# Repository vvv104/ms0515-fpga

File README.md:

# ms0515-fpga

The Elektronika MS 0515 rebuilt in an FPGA down to its circuits: the
system module НС4 (`3.858.420 Э3`) as a netlist of its chips, wired as the
schematic and the board wire them, tested against the emulator
(https://github.com/vvv104/ms0515).

- `docs/sources.md` - the documents, scans and threads it is read from
- `docs/plan.md` - the stages
- `docs/findings.md` - where the sources disagree
- `CLAUDE.md` - the rules of the repository

## The ready files

The releases (https://github.com/vvv104/ms0515-fpga/releases) carry the
MiSTer core (`ms0515.rbf`, for a DE10-Nano) and both printed boards'
Gerbers with their assembly drawings (НС4 and the RAM-disk module);
`docs/release.md` says what to do with each and how to make them again.

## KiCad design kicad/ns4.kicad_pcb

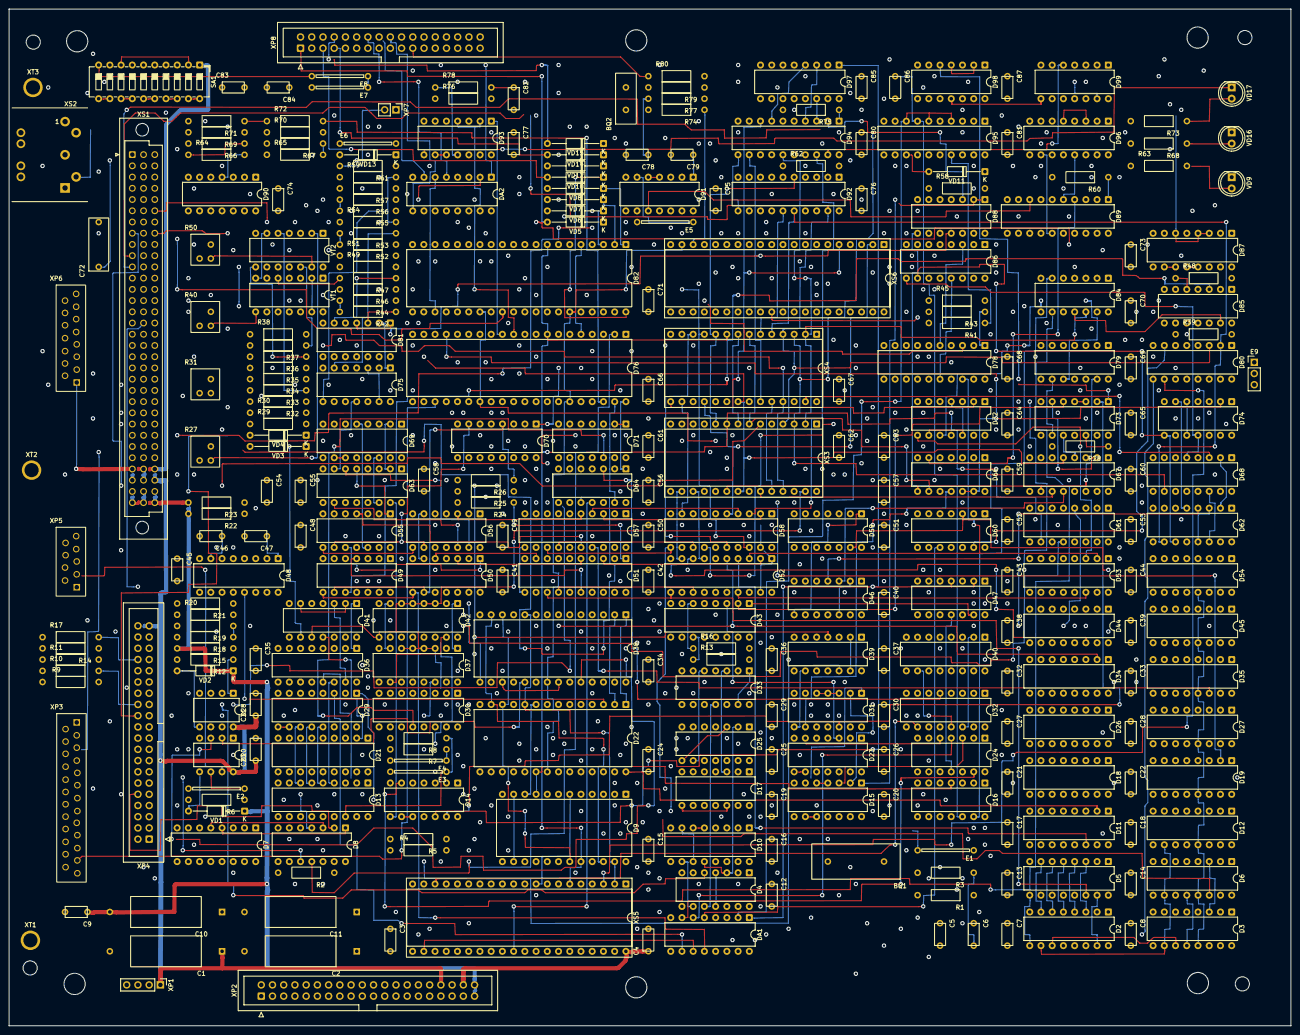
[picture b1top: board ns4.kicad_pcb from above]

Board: 8 copper layers, 290.0 x 230.0 mm, 324 parts (0 on the bottom side), 490 nets.

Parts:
BQ1: 8 МГц; Crystal_RK353_P12.70mm
BQ2: 15 МГц; Crystal_RK169_P5.08mm
C1, C2, C10, C11: 16В 33 мкФ ±20%; CP_Axial_P25.40mm
C3, C4, C7, C8, C9, C12, C13, C14, C15, C16, C17, C18, C19, C20, C21, C22, C23, C24, C25, C26, C27, C28, C29, C30, C31, C32, C33, C34, C36, C37, C38, C39, C41, C42, C43, C44, C48, C49, C50, C51, C52, C53, C55, C56, C57, C58, C59, C60, C61, C62, C63, C65, C66, C67, C68, C69, C71, C73, C75, C76, C77, C80, C81, C85, C87: 0,22 мкФ +80-20%; C_Disc_P5.08mm
C5, C6, C70: 100 пФ ±10%; C_Disc_P5.08mm
C35: 68 пФ ±10%; C_Disc_P5.08mm
C40: 27 пФ ±10%; C_Disc_P5.08mm
C45, C46, C47, C74: 2200 пФ ±10%; C_Disc_P5.08mm
C54: 4700 пФ ±10%; C_Disc_P5.08mm
C64: 120 пФ ±10%; C_Disc_P5.08mm
C72: 2,2 мкФ +80-20%; C_Rect_P10.16mm
C78, C79, C82: 51 пФ ±10%; C_Disc_P5.08mm
C83, C84, C86: 0,1 мкФ +80-20%; C_Disc_P5.08mm
D2, D3, D5, D6, D11, D12, D18, D19, D26, D27, D34, D35, D44, D45, D53, D54: КР565РУ5Г; DIP-16_W7.62mm
D4: К555ТЛ2; DIP-14_W7.62mm
D7: КР531ИД14; DIP-16_W7.62mm
D8: К155ЛП9; DIP-14_W7.62mm
D9: КР580ВИ53; DIP-24_W15.24mm
D10, D97: К555ТМ9; DIP-16_W7.62mm
D13, D21: КР556РТ12; DIP-18_W7.62mm
D14, D66: К555ЛА3; DIP-14_W7.62mm
D15, D91, D99: К555ЛН1; DIP-14_W7.62mm
D16, D46, D59: К555ИЕ19; DIP-14_W7.62mm
D17, D33, D41, D47, D60: К555ТМ2; DIP-14_W7.62mm
D20, D28: КР1102АП15; DIP-8_W7.62mm
D22, D38: КР580ВВ51А; DIP-28_W15.24mm
D23: КР531ЛЕ1; DIP-14_W7.62mm
D24: КР531ТМ2; DIP-14_W7.62mm
D25: К555ЛР11; DIP-14_W7.62mm
D29, D30, D36, D37, D42: К555ИЕ10; DIP-16_W7.62mm
D31: К555ЛА4; DIP-14_W7.62mm
D32, D86: К555КП15; DIP-16_W7.62mm
D39: К555ЛП5; DIP-14_W7.62mm
D40, D43: К555ТМ8; DIP-16_W7.62mm
D48: КР559ИП11; DIP-16_W7.62mm
D49, D50, D55, D56: К555ИР16; DIP-14_W7.62mm
D51, D57, D78, D89: К555ИР23; DIP-20_W7.62mm
D52, D58: К555АП5; DIP-20_W7.62mm
D61, D62, D63, D67, D68, D69, D87: К555КП2; DIP-16_W7.62mm
D64: К555ЛН2; DIP-14_W7.62mm
D70: К555КП11; DIP-16_W7.62mm
D71: К555ЛИ6; DIP-14_W7.62mm
D72, D74, D79, D84: К555ЛЛ1; DIP-14_W7.62mm
D73: К555ЛИ1; DIP-14_W7.62mm
D75: К155ЛН5; DIP-14_W7.62mm
D76, D82: КР580ВВ55А; DIP-40_W15.24mm
D80: К555ИД7; DIP-16_W7.62mm
D81, D93: К555ЛА13; DIP-14_W7.62mm
D85: К555ЛИ3; DIP-14_W7.62mm
D88: К555ЛА2; DIP-14_W7.62mm
D90: К554СА3А; DIP-14_W7.62mm
D92, D94: К555ИР22; DIP-20_W7.62mm
D95: К555АП3; DIP-20_W7.62mm
D96: К555ИВ3; DIP-16_W7.62mm
D98: КР1533ТМ2; DIP-14_W7.62mm
DA1: 3-15-1 кОм ±10%; DIP-16_W7.62mm
DA2: 3-15-10 кОм ±10%; DIP-16_W7.62mm
E1, E2, E3, E4, E5, E6, E7, E8: jumper (two contacts on Э3); Wire_Link_P12.70mm
E9: jumper (three contacts); PinHeader_1x03_P2.54mm_Vertical
H1, H2, H3, H4, H5, H6: Hole_4.8mm_NPTH
H7, H8, H9, H10: Hole_3.2mm_NPTH
R1, R3, R77, R79: 560 Ом; R_Axial_P12.70mm
R2, R6, R12: 10 кОм; R_Axial_P12.70mm
R4, R5, R7, R8, R21, R26, R28, R39, R41, R48, R55, R58, R71, R72, R74, R76, R80: 1 кОм; R_Axial_P12.70mm
R9, R10, R11, R14, R17: 150 Ом; R_Axial_P12.70mm
R13, R16: 33 Ом; R_Axial_P12.70mm
R15, R22, R23: 23,7 кОм ±1%; R_Axial_P12.70mm
R18, R20, R64, R70: 4,7 кОм; R_Axial_P12.70mm
R19: 1,2 кОм; R_Axial_P12.70mm
R24, R25, R43, R45, R60, R62, R75: 20 Ом; R_Axial_P12.70mm
R27, R31, R40, R50: 330 Ом (trimmer); Trimmer_SP5-16VA
R29: 180 Ом; R_Axial_P12.70mm
R30, R33, R35: 24 Ом; R_Axial_P12.70mm
R32, R34, R36, R37, R38: 75 Ом; R_Axial_P12.70mm
R42, R47, R52, R56: 510 Ом; R_Axial_P12.70mm
R44, R49, R53: 390 Ом; R_Axial_P12.70mm
R46, R51, R54, R59: 220 Ом; R_Axial_P12.70mm
R57: 270 Ом; R_Axial_P12.70mm
R61: 43 Ом; R_Axial_P12.70mm
R63, R68, R73: 470 Ом; R_Axial_P12.70mm
R65: 470 кОм; R_Axial_P12.70mm
R66: 24 кОм; R_Axial_P12.70mm
R67: 2,2 кОм; R_Axial_P12.70mm
R69: 12 кОм; R_Axial_P12.70mm
R78: 620 Ом; R_Axial_P12.70mm
R81: 620 кОм ±5%
SA1: switch, 10 pairs; SW_DIP_SPSTx10_Slide_6.7x26.96mm_W7.62mm_P2.54mm_LowProfile
VD1, VD2, VD3, VD4, VD5, VD6, VD7, VD8, VD10, VD12, VD13, VD14, VD15: diode; D_DO-35_SOD27_P12.70mm_Horizontal
VD9, VD16, VD17: LED; LED_D5.0mm
VD11: zener 3,3 В; D_DO-35_SOD27_P12.70mm_Horizontal
VT1, VT2: transistor assembly; DIP-14_W7.62mm
W1: 0.07 мм²
XP1: plug, 4; PinHeader_1x04_P2.54mm_Vertical
XP2, XP4: plug, 40; IDC-Header_2x20_P2.54mm_Vertical
XP3: plug, 25; DSUB-25_ONP-ZhG-79
XP5: plug, 9; DSUB-9_ONP-ZhG-79
XP6: plug, 15; DSUB-15_ONP-ZhG-79
XP7: plug, 2; PinHeader_1x02_P2.54mm_Vertical
XP8: plug, 34; IDC-Header_2x17_P2.54mm_Vertical
XS1: socket, 96 (rows A, B, C of 32); DIN41612_C_3x32_Female_Vertical_THT
XS2: socket, 5; DIN-5_Socket_Horizontal
XS3, XS4: DIP socket for D65, D77; DIP-28_W15.24mm_Socket
XS5, XS6: DIP socket for D1, D83; DIP-40_W15.24mm_Socket
XT1, XT2, XT3: ground lug (ОБЩИЙ); Lug_3.2mm

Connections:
+5V: C2.1, C3.1, C7.1, C8.1, C11.1, C12.1, C13.1, C14.1, C15.1, C16.1, C17.1, C18.1, C19.1, C20.1, C21.1, C22.1, C24.1, C25.1, C26.1, C27.1, C28.1, C29.1, C30.1, C32.1, C33.1, C34.1, C36.1, C37.1, C38.1, C39.1, C41.1, C42.1, C43.1, C44.1, C48.1, C49.1, C50.1, C51.1, C52.1, C53.1, C55.1, C56.1, C57.1, C58.1, C59.1, C60.1, C61.1, C62.1, C63.1, C65.1, C66.1, C67.1, C68.1, C69.1, C71.1, C73.1, C74.1, C75.1, C76.1, C77.1, C80.1, C81.1, C85.1, C87.1, D2.8, D3.8, D4.14, D5.8, D6.8, D7.16, D8.14, D9.24, D10.16, D11.8, D12.8, D13.18, D14.14, D15.14, D16.14, D17.14, D18.8, D19.8, D21.18, D22.26, D23.14, D24.14, D25.14, D26.8, D27.8, D29.16, D30.16, D31.14, D32.16, D33.14, D34.8, D35.8, D36.16, D37.16, D38.26, D39.14, D40.16, D41.14, D42.16, D43.16, D44.8, D45.8, D46.14, D47.14, D48.16, D49.14, D50.14, D51.20, D52.20, D53.8, D54.8, D55.14, D56.14, D57.20, D58.20, D59.14, D60.14, D61.16, D62.16, D63.16, D64.14, D66.14, D67.16, D68.16, D69.16, D70.16, D71.14, D72.14, D73.14, D74.14, D75.14, D76.26, D78.20, D79.14, D80.16, D81.14, D82.26, D84.14, D85.14, D86.16, D87.16, D88.14, D89.20, D90.11, D91.14, D92.20, D93.14, D94.20, D95.20, D96.16, D97.16, D98.14, D99.14, DA1.16, R2.2, R4.2, R5.2, R7.2, R8.2, R9.1, R10.1, R11.1, R14.2, R17.1, R19.2, R20.2, R21.2, R26.2, R27.1, R27.2, R28.2, R29.2, R30.2, R31.1, R31.2, R33.2, R35.2, R37.2, R39.2, R40.1, R40.2, R41.2, R48.2, R50.1, R50.2, R63.2, R67.2, R68.2, R73.2, R76.2, R80.2, VD11.1, VD13.1, XP1.4, XP2.1, XP2.2, XP2.3, XP2.4, XP2.5, XP2.6, XP2.7, XP2.8, XP2.9, XP2.10, XP2.11, XP2.12, XP4.35, XP4.36, XP7.1, XS1.a27, XS1.a28, XS1.b27, XS1.b28, XS1.c27, XS1.c28, XS3.1, XS3.28, XS4.1, XS4.28, XS5.21, XS6.40
+12V: C1.1, C4.1, C23.1, C31.1, D20.8, D28.8, SA1.1, XP1.1, XP2.33, XP2.34, XP2.35, XP2.36, XP2.37, XP2.38, XP4.39, XP4.40, XP6.1, XP6.2, XS1.a29, XS1.a30, XS1.b29, XS1.b30, XS1.c29, XS1.c30, XS5.40
-12V: C9.1, C10.2, R15.2, R22.2, R23.2, VD1.1, VD2.1, XP2.39, XP2.40, XS1.a31, XS1.a32, XS1.b31, XS1.b32, XS1.c31, XS1.c32
G: R36.1, VT2.8, XP6.14
GND: C1.2, C2.2, C3.2, C4.2, C7.2, C8.2, C9.2, C10.1, C11.2, C12.2, C13.2, C14.2, C15.2, C16.2, C17.2, C18.2, C19.2, C20.2, C21.2, C22.2, C23.2, C24.2, C25.2, C26.2, C27.2, C28.2, C29.2, C30.2, C31.2, C32.2, C33.2, C34.2, C35.2, C36.2, C37.2, C38.2, C39.2, C40.2, C41.2, C42.2, C43.2, C44.2, C45.2, C46.2, C47.2, C48.2, C49.2, C50.2, C51.2, C52.2, C53.2, C54.2, C55.2, C56.2, C57.2, C58.2, C59.2, C60.2, C61.2, C62.2, C63.2, C64.2, C65.2, C66.2, C67.2, C68.2, C69.2, C70.2, C71.2, C73.2, C74.2, C75.2, C76.2, C77.2, C80.2, C81.2, C82.2, C83.2, C85.2, C86.2, C87.2, D2.16, D3.16, D4.7, D5.16, D6.16, D7.1, D7.8, D8.7, D9.12, D10.8, D11.16, D12.16, D13.8, D13.9, D13.10, D14.7, D15.7, D16.2, D16.7, D17.7, D18.16, D19.16, D20.4, D21.8, D21.9, D21.10, D21.15, D21.16, D22.4, D22.17, D22.22, D23.7, D24.7, D25.4, D25.5, D25.7, D26.16, D27.16, D28.4, D29.8, D30.8, D31.7, D32.7, D32.8, D32.12, D33.7, D34.16, D35.16, D36.8, D37.8, D38.4, D39.7, D40.8, D40.13, D41.7, D42.8, D43.8, D44.16, D45.16, D46.7, D47.7, D48.2, D48.4, D48.6, D48.8, D48.12, D48.14, D49.7, D50.7, D51.10, D52.10, D53.16, D54.16, D55.7, D56.1, D56.7, D57.10, D58.10, D59.7, D59.12, D60.7, D61.1, D61.8, D61.15, D62.1, D62.8, D62.15, D63.8, D64.7, D66.7, D67.1, D67.8, D67.15, D68.1, D68.8, D68.15, D69.8, D70.8, D71.7, D72.7, D73.7, D74.7, D75.7, D76.7, D78.10, D79.7, D80.8, D81.7, D82.7, D84.7, D85.7, D86.8, D87.1, D87.8, D87.15, D88.7, D89.10, D90.2, D90.6, D91.7, D92.10, D93.7, D94.10, D95.2, D95.10, D95.19, D96.8, D97.8, D98.7, D99.7, E3.2, E4.2, R6.2, R12.2, R18.2, R24.2, R25.2, R32.2, R34.2, R36.2, R38.2, R43.2, R45.2, R46.2, R51.2, R58.2, R60.2, R62.2, R66.2, R69.2, R70.1, R71.2, R74.2, R75.2, SA1.4, SA1.7, VD4.1, XP1.2, XP1.3, XP2.13, XP2.14, XP2.15, XP2.16, XP2.17, XP2.18, XP2.19, XP2.20, XP2.21, XP2.22, XP2.23, XP2.24, XP2.25, XP2.26, XP2.27, XP2.28, XP2.29, XP2.30, XP2.31, XP2.32, XP4.1, XP4.3, XP4.5, XP4.7, XP4.9, XP4.11, XP4.13, XP4.15, XP4.17, XP4.19, XP4.21, XP4.23, XP4.25, XP4.27, XP4.29, XP4.31, XP4.33, XP4.37, XP4.38, XP5.1, XP5.8, XP6.3, XP6.4, XP6.5, XP6.6, XP6.7, XP6.8, XP8.9, XS1.a1, XS1.a2, XS1.a19, XS1.a20, XS1.a25, XS1.a26, XS1.b1, XS1.b2, XS1.b19, XS1.b20, XS1.b25, XS1.b26, XS1.c1, XS1.c2, XS1.c15, XS1.c16, XS1.c19, XS1.c20, XS1.c25, XS1.c26, XS3.14, XS4.14, XS5.20, XS5.37, XS6.8, XS6.20, XS6.23, XT1.1, XT2.1, XT3.1
R: R34.1, VT2.7, XP6.13
~C5.2: BQ1.1, C5.2
~C72.2: C72.2, R64.1, R66.1
~C79.2: BQ2.1, C79.2
~D1.23: R2.1, XS5.23
~D4.8: D4.8, D25.1
~D4.10: D4.10, D33.11
~D4.12: D4.12, D47.3
~D7.4: D7.4, D8.1
~D7.5: D7.5, D8.3
~D7.6: D7.6, D8.5
~D7.7: D7.7, D8.9
~D10.2: D10.2, D25.10
~D10.5: D10.5, D10.6
~D10.7: D10.7, D10.11
~D10.10: D4.9, D10.10, D10.13
~D10.12: D4.3, D10.12, D25.2, D33.2, D33.10
~D14.3: D14.3, D70.15, D74.1
~D14.6: D14.6, D84.9
~D14.11: D14.11, D43.1, D47.13
~D15.4: D15.4, D15.5
~D15.6: D15.6, D31.1
~D15.8: D15.8, E1.1
~D15.11: C6.2, D15.11, R3.1
~D15.12: C6.1, D15.12, R1.2
~D15.13: C5.1, D15.13, R1.1
~D17.6: D17.6, D33.12
~D17.8: D17.8, D17.12
~D20.1: D20.1, R6.1
~D20.5: D20.5, VD1.2
~D20.6: D20.6, E2.1
~D23.4: D23.4, D24.12
~D23.13: D23.13, D79.4
~D24.5: D23.6, D24.5
~D24.6: D24.6, D31.13
~D24.9: D23.5, D24.9
~D25.6: D10.4, D25.6
~D28.1: D28.1, R12.1
~D28.5: D28.5, VD2.2
~D29.15: D29.15, D36.7
~D30.15: D30.15, D37.7, D42.7
~D31.8: D31.8, D39.9
~D33.5: D25.9, D33.5
~D33.6: D25.12, D33.6
~D33.8: D25.11, D25.13, D33.8
~D33.9: D17.1, D33.9
~D36.15: D36.15, D41.3
~D40.2: D32.14, D40.2, D40.5
~D40.7: D32.1, D32.2, D32.3, D32.4, D32.15, D40.7, D40.12
~D40.10: D32.13, D40.10
~D41.6: D41.2, D41.6
~D42.15: D37.10, D42.15
~D43.2: D43.2, D73.5
~D43.3: D23.3, D43.3
~D43.6: D4.1, D43.6, R16.1
~D43.7: D43.7, D43.12
~D43.10: D43.10, D43.13
~D43.11: D43.11, R13.1
~D43.15: D43.15, D47.12
~D47.8: D23.2, D47.8
~D47.9: C40.1, D14.12, D47.9
~D48.10: D48.10, R18.1, R19.1
~D48.11: D48.11, D66.4
~D49.10: D49.10, D85.3
~D50.10: D49.1, D50.10
~D51.1: D51.1, R24.1
~D57.1: D57.1, R25.1
~D64.2: D64.2, VD9.1
~D64.12: D64.12, VD16.1
~D66.3: D7.15, D66.3
~D69.9: D69.9, D81.1, D81.4, D81.9
~D71.8: D70.5, D70.10, D71.1, D71.2, D71.4, D71.5, D71.8
~D72.3: D7.13, D72.3
~D75.2: D75.2, R44.1
~D75.4: D75.4, R49.1
~D75.6: D75.6, R53.1
~D75.10: D75.10, R55.1
~D75.12: D75.12, R56.1
~D78.1: D78.1, R43.1
~D78.2: D78.2, D86.4
~D78.5: D78.5, D86.3
~D78.6: D78.6, D86.2
~D78.9: D78.9, D86.1
~D78.12: D78.12, D86.15
~D78.15: D78.15, D86.14
~D78.16: D78.16, D86.13
~D79.6: D43.5, D79.6
~D79.8: D41.12, D79.8
~D80.15: D79.2, D80.15
~D81.3: D81.3, R42.1
~D81.6: D81.6, R47.1
~D81.8: D81.8, R52.1
~D81.11: D81.11, R57.1
~D83.21: D99.1, XS6.21
~D84.6: D16.13, D84.6
~D84.11: D84.11, D85.13
~D86.7: D86.7, R45.1
~D87.7: D85.10, D87.7
~D87.9: D85.11, D87.9
~D89.1: D89.1, R60.1
~D89.2: D89.2, D96.12
~D89.5: D89.5, D96.13
~D89.6: D89.6, D96.1
~D89.9: D89.9, D96.2
~D89.12: D89.12, D96.4
~D89.15: D89.15, D96.10
~D90.3: D90.3, R65.1, R70.2
~D90.4: D90.4, R64.2
~D91.1: C79.1, D91.1, R77.1
~D91.2: C78.1, D91.2, R77.2
~D91.3: C78.2, D91.3, R79.1
~D91.4: BQ2.2, D91.4, D91.5, R79.2
~D91.6: D91.6, E5.1
~D91.8: D60.11, D91.8
~D92.1: D92.1, R62.1
~D93.3: D93.3, D93.6, R61.1, VD13.2
~D93.8: D93.8, VD17.1
~D93.11: D93.11, R76.1, R78.1
~D94.1: D94.1, R75.1
~D95.7: C86.1, D16.12, D95.7
~D99.6: D87.10, D87.11, D99.6
~D99.10: D87.3, D87.4, D87.6, D99.10
~E1.2: D16.1, E1.2
~E6.2: E6.2, XP6.11
~E9.2: D80.5, E9.2
~R61.2: E6.1, R61.2, XP7.2
~R72.1: C83.1, C84.1, R71.1, R72.1
~R78.2: C82.1, D47.1, R78.2
~SA1.6: E7.2, SA1.6
~SA1.10: E8.2, SA1.10
~VD3.2: VD3.1, VD4.2
~VD9.1: R63.1, VD9.2
~VD11.1: D95.13, R58.1, VD11.2
~VD16.1: R68.1, VD16.2
~VD17.1: R73.1, VD17.2
~VT1.B: C54.1, R29.1, VD3.2, VT1.2, VT1.6, VT1.9, VT1.13
~VT1.C1: R27.3, VT1.1, VT2.2
~VT1.C2: R31.3, VT1.7, VT2.6
~VT1.C3: R40.3, VT1.8, VT2.9
~VT1.C4: R50.3, VT1.14, VT2.13
~VT1.E1: R42.2, R44.2, R46.1, VT1.3
~VT1.E2: R47.2, R49.2, R51.1, VT1.5
~VT1.E3: R52.2, R53.2, R54.1, VT1.10
~VT1.E4: R55.2, R56.2, R57.2, R59.1, VT1.12
~VT2.E1: R30.1, VT2.3
~VT2.E2: R33.1, VT2.5
~VT2.E3: R35.1, VT2.10
~VT2.E4: R37.1, VT2.12
~XP5.3: C47.1, D48.1, R22.1, XP5.3
~XP5.5: E2.2, XP5.5
~XP5.6: C46.1, D48.7, R23.1, XP5.6
~XP8.1: VD5.2, XP8.1
~XP8.2: VD6.2, XP8.2
~XP8.3: VD7.2, XP8.3
~XP8.4: VD8.2, XP8.4
~XP8.5: VD10.2, XP8.5
~XP8.6: VD12.2, XP8.6
~XP8.7: VD14.2, XP8.7
~XP8.8: VD15.2, XP8.8
~XS2.1: SA1.19, SA1.20, XS2.1
~XS2.2: SA1.17, SA1.18, XS2.2
~XS2.3: SA1.15, SA1.16, XS2.3
~XS2.4: SA1.13, SA1.14, XS2.4
~XS2.5: SA1.11, SA1.12, XS2.5
А0 H: D2.5, D3.5, D5.5, D6.5, D11.5, D12.5, D18.5, D19.5, D26.5, D27.5, D34.5, D35.5, D44.5, D45.5, D53.5, D54.5, D61.7
А1 H: D2.7, D3.7, D5.7, D6.7, D11.7, D12.7, D18.7, D19.7, D26.7, D27.7, D34.7, D35.7, D44.7, D45.7, D53.7, D54.7, D61.9
А2 H: D2.6, D3.6, D5.6, D6.6, D11.6, D12.6, D18.6, D19.6, D26.6, D27.6, D34.6, D35.6, D44.6, D45.6, D53.6, D54.6, D67.7
А3 H: D2.12, D3.12, D5.12, D6.12, D11.12, D12.12, D18.12, D19.12, D26.12, D27.12, D34.12, D35.12, D44.12, D45.12, D53.12, D54.12, D67.9
А4 H: D2.11, D3.11, D5.11, D6.11, D11.11, D12.11, D18.11, D19.11, D26.11, D27.11, D34.11, D35.11, D44.11, D45.11, D53.11, D54.11, D62.7
А5 H: D2.10, D3.10, D5.10, D6.10, D11.10, D12.10, D18.10, D19.10, D26.10, D27.10, D34.10, D35.10, D44.10, D45.10, D53.10, D54.10, D62.9
А6 H: D2.13, D3.13, D5.13, D6.13, D11.13, D12.13, D18.13, D19.13, D26.13, D27.13, D34.13, D35.13, D44.13, D45.13, D53.13, D54.13, D68.7
А7 H: D2.9, D3.9, D5.9, D6.9, D11.9, D12.9, D18.9, D19.9, D26.9, D27.9, D34.9, D35.9, D44.9, D45.9, D53.9, D54.9, D68.9
А13 H: D62.5, D74.6, D86.11
А14 H: D62.11, D74.8, D86.10
А15 H: D68.5, D74.11, D86.9
АВ01 H: D21.6, D42.14, D61.4
АВ02 H: D21.7, D42.13, D61.12
АВ03 H: D21.4, D42.12, D67.4, D73.10
АВ04 H: D46.3, D67.12
АВ05 H: D46.4, D62.4
АВ06 H: D46.5, D62.12
АВ07 H: D46.6, D46.13, D68.4
АВ08 H: D46.11, D68.12
АВ09 H: D46.10, D61.3
АВ10 H: D46.9, D61.13
АВ11 H: D46.8, D59.1, D67.3
АВ12 H: D59.3, D67.13
АВ13 H: D59.4, D68.13
АД00 H: D92.2, XS1.a3
АД01 H: D9.19, D22.12, D38.12, D61.6, D76.9, D82.9, D92.5, XS1.a4, XS3.10, XS4.10, XS5.5
АД02 H: D9.20, D61.10, D76.8, D82.8, D92.6, XS1.a5, XS3.9, XS4.9, XS5.6
АД03 H: D67.6, D92.9, E9.3, XS1.a6, XS3.8, XS4.8
АД04 H: D67.10, D79.13, D92.12, XS1.a7, XS3.7, XS4.7
АД05 H: D62.6, D80.1, D92.15, XS1.a8, XS3.6, XS4.6
АД06 H: D62.10, D80.2, D92.16, XS1.a9, XS3.5, XS4.5
АД07 H: D68.6, D80.3, D92.19, XS1.a10, XS3.4, XS4.4
АД08 H: D68.10, D88.3, D94.2, XS1.a11, XS3.3, XS4.3
АД09 H: D61.5, D88.4, D94.5, XS1.a12, XS3.25, XS4.25
АД10 H: D61.11, D88.5, D94.6, XS1.a13, XS3.24, XS4.24
АД11 H: D67.5, D88.6, D94.9, XS1.a14, XS3.21, XS4.21
АД12 H: D67.11, D88.11, D94.12, XS1.a15, XS3.23, XS4.23
АД13 H: D74.4, D84.12, D86.12, D88.12, D94.15, XS1.a16, XS3.2, XS4.2
АД14 H: D74.9, D85.1, D87.5, D94.16, D99.11, XS1.a17
АД15 H: D74.12, D85.2, D87.12, D87.13, D94.19, D99.5, XS1.a18
АПК1 H: D13.5, D29.13
АПК2 H: D13.6, D29.12
АПК3 H: D13.7, D29.11
АПК4 H: D13.4, D36.14
АПК5 H: D13.3, D36.13
АПК6 H: D13.2, D36.12
АПК7 H: D13.1, D36.11, D84.4
АПК8 H: D13.17, D41.5
АРБ H: D43.4, D73.3, D73.4
БАНК7 H: D74.5, D74.10, D74.13, D85.8
БЛНК H: D31.11, D50.1, D55.10
БОРДК L: D13.14, D14.2, D85.5, R48.1
БОРДС L: C70.1, D14.1, D21.14, D73.9, D79.9, D85.4, R39.1
В: R32.1, VT2.1, XP6.15
ВАК L: D2.15, D3.15, D5.15, D6.15, D11.15, D12.15, D18.15, D19.15, D26.15, D27.15, D34.15, D35.15, D44.15, D45.15, D53.15, D54.15, R13.2
ВАС L: D2.4, D3.4, D5.4, D6.4, D11.4, D12.4, D18.4, D19.4, D26.4, D27.4, D34.4, D35.4, D44.4, D45.4, D53.4, D54.4, R16.2
ВБ0 H: D4.2, D61.14, D62.14, D67.14, D68.14
ВБ1 H: D61.2, D62.2, D67.2, D68.2, D73.6, D79.5
ВБ7 H: D78.19, D85.9
ВБ53 L: D9.21, D80.13
ВБ55 L: D80.12, D82.6
ВБ93 L: D80.10, XS5.3
ВБ511 L: D22.11, D80.14
ВБ512 L: D38.11, D80.9
ВБ СИР L: D76.6, D80.11
ВБКЛ L: D48.9, DA2.16, R20.1
ВБП H: D8.12, XP4.32
ВБРЕГ L: D66.9, D80.4, D88.8, D98.12, E9.1
ВБРПЗУ L: D66.8, XS3.20, XS4.20
ВК2 H: D49.9, D50.9, D70.4, R26.1
ВК3 H: D55.9, D56.9, D70.7
ВК4 H: D49.6, D50.6, D55.6, D56.6, D70.9
ВК5 H: D63.2, D69.2, D74.3
ВК7 H: D14.8, D63.1, D63.15, D69.1, D69.15
ВК8 H: D39.8, D63.14, D69.14
ВКЛДВ H: D8.11, D76.2
ВН0 H: D8.2, XP4.10
ВН1 H: D8.4, XP4.12
ВН2 H: D8.6, XP4.14
ВН3 H: D8.8, XP4.6
ВТАКТ H: D46.1, D73.8
ВУ H: D15.1, D66.10, D85.12, D88.1, D88.2, XS1.c14
ВУ L: D15.2, D24.2, D31.2
ВХКЛ L: C45.1, D48.15, R15.1, SA1.5, XP6.10
ВЫХКЛ L: D28.7, SA1.3, XP6.9
ГОТ93 H: D76.18, XS5.39
ГОТОВ2 L: D38.17, D38.22, D48.5
ГТВ H: D4.6, D76.20, XS5.32
ГТВ L: D4.5, R17.2, XP4.34
Д00 H: D2.14, D51.3, D52.2
Д01 H: D11.14, D51.4, D52.4
Д02 H: D26.14, D51.7, D52.6
Д03 H: D44.14, D51.8, D52.8
Д04 H: D5.14, D51.13, D52.11
Д05 H: D18.14, D51.14, D52.13
Д06 H: D34.14, D51.17, D52.15
Д07 H: D51.18, D52.17, D53.14
Д08 H: D3.14, D57.3, D58.2
Д09 H: D12.14, D57.4, D58.4
Д10 H: D27.14, D57.7, D58.6
Д11 H: D45.14, D57.8, D58.8
Д12 H: D6.14, D57.13, D58.11
Д13 H: D19.14, D57.14, D58.13
Д14 H: D35.14, D57.17, D58.15
Д15 H: D54.14, D57.18, D58.17
ДВ00 H: D50.2, D51.2
ДВ01 H: D50.3, D51.5
ДВ02 H: D50.4, D51.6
ДВ03 H: D50.5, D51.9
ДВ04 H: D49.2, D51.12
ДВ05 H: D49.3, D51.15
ДВ06 H: D49.4, D51.16
ДВ07 H: D49.5, D51.19
ДВ08 H: D56.2, D57.2
ДВ09 H: D56.3, D57.5
ДВ10 H: D56.4, D57.6
ДВ11 H: D56.5, D57.9
ДВ12 H: D55.2, D57.12
ДВ13 H: D55.3, D57.15
ДВ14 H: D55.4, D57.16
ДВ15 H: D55.5, D57.19
ДВ H: D8.10, XP4.16
ДЗП L: D9.23, D22.10, D38.10, D76.36, D79.1, D82.36, D84.3, XS1.c4, XS5.2
ДКЛ00 L: D82.4, VD5.1, XP3.2
ДКЛ01 L: D82.3, VD6.1, XP3.3
ДКЛ02 L: D82.2, VD7.1, XP3.4
ДКЛ03 L: D82.1, VD8.1, XP3.5
ДКЛ04 L: D82.40, VD10.1, XP3.6
ДКЛ05 L: D82.39, VD12.1, XP3.7
ДКЛ06 L: D82.38, VD14.1, XP3.8
ДКЛ07 L: D82.37, VD15.1, XP3.9
ДКЛ08 L: D82.18, DA2.1, XP8.10
ДКЛ09 L: D82.19, DA2.2, XP8.11
ДКЛ10 L: D82.20, DA2.3, XP8.12
ДКЛ11 L: D82.21, DA2.4, XP8.13
ДКЛ12 L: D82.22, DA2.5, XP8.14
ДКЛ13 L: D82.23, DA2.6, XP8.15
ДКЛ14 L: D82.24, DA2.7, XP8.16
ДКЛ15 L: D82.25, DA2.8, XP8.17
ДКЛ16 L: D82.14, DA2.9, XP8.18
ДКЛ17 L: D82.15, DA2.10, XP8.19
ДКЛ18 L: D82.16, DA2.11, XP8.20
ДОР43 H: D32.9, XS5.29
ДПЗУ H: D76.37, D84.13
ДПСЛ H: D39.10, D85.6
ДРОО H: R10.2, XP4.26, XS5.34
ДЧТ L: D72.13, D76.5, D79.12, D82.5, D84.8, XS1.c3, XS3.22, XS4.22, XS5.4
ЗАВЕРШ H: D76.24, XP3.11
ЗАДЕРЖ L: D98.9, XS6.26
ЗАП H: D32.5, D64.3
ЗАП L: D64.4, XP4.22
ЗАП МАГ H: C84.2, SA1.2, SA1.8
ЗАП РЕГ H: D78.11, D79.3, D97.9
ЗАПР 7007 L: D66.6, D89.4
ЗАПР Д С2 L: D89.7, D99.12
ЗАПР КЛ L: D89.14, D91.12
ЗАПР М С2 L: D89.8, D91.10
ЗАПР МОН H: D95.11, D97.15
ЗАПР МОН L: D89.3, D95.9
ЗАПР ОСТ L: D60.8, D89.17
ЗАПР ТАЙМ L: D60.6, D89.13
ЗАПРД H: D38.15, D99.13
ЗАПРМ H: D38.14, D91.11
ЗЗП H: R11.2, XP4.28, XS5.36
ЗЛ H: D56.11, D69.6
ЗЛФ H: D55.12, D69.5
ЗОВМ H: D76.19, XS5.38
ЗП МЛ L: D2.3, D5.3, D11.3, D18.3, D26.3, D34.3, D44.3, D53.3, D72.8
ЗП СТ L: D3.3, D6.3, D12.3, D19.3, D27.3, D35.3, D45.3, D54.3, D72.6
ЗЦ H: D69.7, D75.5, D81.10, D81.12, D81.13
ИМП ЗП H: D40.4, XS5.31
ИМП ЧТ H: D17.3, D33.3, D47.5, D93.12, D93.13
ИМП ЧТ L: D47.6, XS5.27
ИНД1 H: D64.1, D76.40
ИНД2 H: D64.13, D76.39
ИНД3 H: D69.12, D69.13, D76.13, D93.9, D93.10
ИНД H: R9.2, XP4.8, XS5.35
ИНТ H: D55.11, D69.10, D69.11
КР H: D56.12, D63.10
КРФ H: D55.13, D63.11
КСИ H: D41.8, D59.13, D60.3
КСИ L: D41.9, D73.13, D79.10
КЦ H: D63.9, D75.3, D75.13, D81.5
МК00 H: D2.2, D9.8, D22.27, D38.27, D52.18, D76.34, D78.3, D82.34, D92.3, XS1.b3, XS3.11, XS5.7, XS6.17
МК01 H: D9.7, D11.2, D22.28, D38.28, D52.16, D76.33, D78.4, D82.33, D92.4, XS1.b4, XS3.12, XS5.8, XS6.16
МК02 H: D9.6, D22.1, D26.2, D38.1, D52.14, D76.32, D78.7, D82.32, D92.7, XS1.b5, XS3.13, XS5.9, XS6.15
МК03 H: D9.5, D22.2, D38.2, D44.2, D52.12, D76.31, D78.8, D82.31, D92.8, XS1.b6, XS3.15, XS5.10, XS6.14
МК04 H: D5.2, D9.4, D22.5, D38.5, D52.9, D76.30, D78.13, D82.30, D92.13, XS1.b7, XS3.16, XS5.11, XS6.13
МК05 H: D9.3, D18.2, D22.6, D38.6, D52.7, D76.29, D78.14, D82.29, D92.14, XS1.b8, XS3.17, XS5.12, XS6.12
МК06 H: D9.2, D22.7, D34.2, D38.7, D52.5, D76.28, D78.17, D82.28, D92.17, XS1.b9, XS3.18, XS5.13, XS6.11
МК07 H: D9.1, D22.8, D38.8, D52.3, D53.2, D76.27, D78.18, D82.27, D92.18, XS1.b10, XS3.19, XS5.14, XS6.10
МК08 H: D3.2, D7.14, D58.18, D94.3, D95.12, D97.14, XS1.b11, XS4.11, XS6.9
МК09 H: D12.2, D58.16, D94.4, D95.18, D97.3, XS1.b12, XS4.12, XS6.7
МК10 H: D27.2, D58.14, D72.1, D94.7, D95.14, D97.4, XS1.b13, XS4.13, XS6.6
МК11 H: D45.2, D58.12, D72.2, D94.8, D95.16, D97.6, XS1.b14, XS4.15, XS6.5
МК12 H: D6.2, D58.9, D94.13, D97.11, XS1.b15, XS4.16, XS6.4
МК13 H: D19.2, D58.7, D94.14, D97.13, XS1.b16, XS4.17, XS6.3
МК14 H: D35.2, D58.5, D94.17, XS1.b17, XS4.18, XS6.2
МК15 H: D54.2, D58.3, D94.18, XS1.b18, XS4.19, XS6.1
МОНО: R38.1, VT2.14, XP6.12
НАЧ H: D97.12, XP3.13
НПР H: D64.9, XS5.16
НПР L: D64.8, XP4.18
ОБСЛ H: D76.23, XP3.12
ОКЗЛ H: D39.12, D69.3, D76.16
ОККР H: D39.4, D63.13, D76.15
ОКРЗЛ H: D39.11, D69.4
ОКРКР H: D39.6, D63.12
ОКРСН H: D39.3, D63.4
ОКСН H: D39.1, D63.3, D76.14
ОСТ L: D91.9, R80.1, XP8.21
ОСТАНОВ L: D89.16, XS6.39
ПВАК H: D89.11, D98.11, D99.8
ПВАК L: D23.12, D84.1, D84.10, D99.9, XS1.c6, XS6.30
ПВАС H: D15.3, D24.3, D66.1, D80.6, D99.4
ПВАС L: D92.11, D94.11, D99.3, XS1.c5, XS6.29
ПКЛ H: D59.9, D66.5
ПКСИ L: D13.12, D41.13, R21.1
ПМЛБ L: D14.4, D72.10, D84.2, XS1.c7, XS6.28
ПОВЕР H: D8.13, D76.1
ПРВ H: XS1.c13, XS6.31
ПРД1 H: D22.19, D28.2
ПРД2 H: D20.2, D38.19
ПРДМАГ H: D76.38, R72.2
ПРМ1 H: D22.3, D48.13
ПРМ2 H: D38.3, D48.3
ПРМАГ H: D76.25, D90.9, R65.2, R67.1
ПСИНХ H: D98.10, D99.2, XS1.c9
ПСС H: D73.11, D75.9
ПСС L: D75.8, R54.2, R59.2
ПСТБ L: D14.5, D72.5, XS1.c8, XS6.27
ПТС H: D24.8, XS6.22
Р1 H: D47.2, D47.4, D97.1, DA1.1
Р2 H: D95.4, D95.6, D95.8, DA1.2
Р3 H: D30.1, D30.3, D30.4, D30.5, D30.6, D30.7, D30.9, D30.10, D37.3, D37.4, D37.5, D37.6, D37.9, D41.10, D42.3, D42.4, D42.5, D42.6, D42.9, D62.3, D62.13, D68.3, DA1.3, XS3.27, XS4.27, XS6.37, XS6.38
Р4 H: D60.4, D96.3, D96.5, D96.11, DA1.4
Р5 H: D60.10, D60.12, D98.2, D98.4, DA1.5
Р6 H: D24.4, DA1.6
Р7 H: D24.10, D24.13, DA1.7
Р8 H: D98.13, DA1.8
Р9 H: D42.10, D47.10, DA1.9
Р10 H: D29.3, D29.4, D29.5, D29.6, D29.7, D29.9, D29.10, D36.3, D36.4, D36.5, D36.6, D36.9, D36.10, DA1.10
Р11 H: D41.4, DA1.11, XS5.22
Р12 H: D49.8, D50.8, DA1.12
Р13 H: D17.10, D17.13, D55.8, D56.8, DA1.13
Р14 H: D9.11, D9.14, D17.2, D17.4, D33.4, DA1.14
Р15 H: D40.1, DA1.15, XS6.32
РАЗР H: D39.2, D39.5, D39.13, D66.12, D66.13, D70.1, D74.2, D76.17
РАЗР L: D31.9, D66.11
РАЗР ГР H: D76.11, D93.2, D93.4
РАЗР ОЗУ L: D14.13, D23.11, D31.12, D72.4, D72.9, D72.12, D73.2
РАСШ H: D68.11, D86.5
РВБ0 H: D87.14, D97.5
РВБ1 H: D87.2, D97.7
РВК0 H: D13.15, D21.17, D76.21, E4.1, R7.1
РВК1 H: D13.16, D76.22, E3.1, R8.1
РВУ0 H: D7.2, D76.4
РВУ1 H: D7.3, D76.3
РЕЖ0 H: XS1.c11, XS6.25
РЕЖ1 H: D66.2, XS1.c10, XS6.24
РЗП H: D64.11, XS5.30
РЗП L: D64.10, XP4.24
РООД1 L: D22.24, D28.3
РООД2 L: D20.3, D38.24
РПРРТ H: D60.2, D97.2
СБР ОСТ L: D60.13, D80.7
СБРАВ H: D46.2, D46.12, D59.2, D95.3
СБРВЗУ L: D95.5, D98.1
СБРКС L: D13.11, D29.1, D36.1, D41.1, D95.17, R41.1
СБРСС L: D21.11, D37.1, D42.1, R4.1
СБРТ L: D7.12, D60.1
СГИ L: C35.1, D13.13, D14.9, D14.10, D21.13, R5.1
СДЛВ H: D32.11, XS5.17
СДПР H: D32.10, XS5.18
СИГН L: D25.3, D25.8
СИНТ H: D9.16, D76.10
СИНХР1 H: D9.10, D22.9, D22.25
СИНХР2 H: D9.13, D38.9, D38.25
СИНХР3 H: D9.17, D23.8, D23.9
СИНХР3 L: D23.10, D93.5
СН H: D56.13, D63.6
СНФ H: D55.1, D56.10, D63.5
СР0 L: D96.9, XS6.36
СР1 L: D96.7, XS6.35
СР2 L: D96.14, XS6.34
СР3 L: D96.6, XS6.33
ССИ L: C64.1, D21.12, D29.2, D36.2, D73.12, R28.1
СТ1 H: D16.9, D84.5
СТАРТ H: D16.10, D22.21, D38.21, D76.35, D82.35, XS6.19
СТРБ H: D97.10, XP3.1
СТРОБ H: D70.11, D71.6, D98.3
СТРОБ ЧТ L: D52.1, D52.19, D58.1, D58.19, D72.11
СТЫК С2 103: D20.7, XP5.2
СТЫК С2 108: D28.6, SA1.9
СЦ H: D63.7, D75.1, D75.11, D81.2
ТАКТ H: D17.9, XS5.26
ТМ H: D31.10, D59.8
ТПРКЛ H: D22.14, D91.13
ТРВЗУ H: D24.1, D73.1, D98.5
ТС1 H: D30.14, D70.2, D71.9
ТС1М H: D16.5, XS5.24
ТС2 H: D30.13, D71.10
ТС2М H: D9.9, D9.15, D9.18, D16.4, D22.20, D38.20
ТС3 H: D30.12, D71.12
ТС4 H: D21.5, D30.11, D71.13
ТС4М H: D10.9, D16.3
ТС5 H: D21.3, D42.11
ТС6 H: D21.2, D37.14, D41.11
ТС7 H: D21.1, D37.13
ТС8М L: BQ1.2, D15.9, D15.10, D40.9, R3.2
ТС15 H: D30.2, D31.3, D31.4, D31.5, D37.2, D42.2, E5.2
ТС15 L: D24.11, D31.6, D43.9, D47.11, D70.3, D70.6
УПР ГР H: D76.12, D93.1
УСТ L: D10.1, D33.1, D33.13, D95.1, R74.1, XS1.c12, XS5.19, XS6.18
ФАЗА H: D4.4, D4.11, D10.3, D17.11
ЧТ51 L: D9.22, D22.13, D38.13, D79.11
ЧТ ВЗУ H: D23.1, D51.11, D57.11, D95.15
ЧТМАГ H: C72.1, E7.1, E8.1, R69.1
ЧТН H: D4.13, R14.1, XP4.30
ШАГ H: D64.5, XS5.15
ШАГ L: D64.6, XP4.20

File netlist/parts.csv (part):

# НС4 parts: 3.858.420 ПЭ3 (mc0515-ed pages 23-26) and the power table
# of 3.858.420 Э3 sheet 1 (page 18).  Power pins (gnd/vcc/vcc12) are
# the power table's; К555 parts may be fitted as КР1533 (ПЭ3 note).
ref,type,value,pins,gnd,vcc,vcc12,source,note
BQ1,РК 353БВ-11А4,8 МГц,2,,,,ПЭ3 p23,
BQ2,РК 169МА-6АН,15 МГц,2,,,,ПЭ3 p23,
C1,К53-14,16В 33 мкФ ±20%,2,,,,ПЭ3 p23,
C2,К53-14,16В 33 мкФ ±20%,2,,,,ПЭ3 p23,
C3,К10-17-2б-Н90,"0,22 мкФ +80-20%",2,,,,ПЭ3 p23,
C4,К10-17-2б-Н90,"0,22 мкФ +80-20%",2,,,,ПЭ3 p23,
C5,К10-17-1б-М47,100 пФ ±10%,2,,,,ПЭ3 p23,
C6,К10-17-1б-М47,100 пФ ±10%,2,,,,ПЭ3 p23,
C7,К10-17-2б-Н90,"0,22 мкФ +80-20%",2,,,,ПЭ3 p23,
C8,К10-17-2б-Н90,"0,22 мкФ +80-20%",2,,,,ПЭ3 p23,
C9,К10-17-2б-Н90,"0,22 мкФ +80-20%",2,,,,ПЭ3 p23,
C10,К53-14,16В 33 мкФ ±20%,2,,,,ПЭ3 p23,
C11,К53-14,16В 33 мкФ ±20%,2,,,,ПЭ3 p23,
C12,К10-17-2б-Н90,"0,22 мкФ +80-20%",2,,,,ПЭ3 p23,
C13,К10-17-2б-Н90,"0,22 мкФ +80-20%",2,,,,ПЭ3 p23,
C14,К10-17-2б-Н90,"0,22 мкФ +80-20%",2,,,,ПЭ3 p23,
C15,К10-17-2б-Н90,"0,22 мкФ +80-20%",2,,,,ПЭ3 p23,
C16,К10-17-2б-Н90,"0,22 мкФ +80-20%",2,,,,ПЭ3 p23,
C17,К10-17-2б-Н90,"0,22 мкФ +80-20%",2,,,,ПЭ3 p23,
C18,К10-17-2б-Н90,"0,22 мкФ +80-20%",2,,,,ПЭ3 p23,
C19,К10-17-2б-Н90,"0,22 мкФ +80-20%",2,,,,ПЭ3 p23,
C20,К10-17-2б-Н90,"0,22 мкФ +80-20%",2,,,,ПЭ3 p23,
C21,К10-17-2б-Н90,"0,22 мкФ +80-20%",2,,,,ПЭ3 p23,
C22,К10-17-2б-Н90,"0,22 мкФ +80-20%",2,,,,ПЭ3 p23,
C23,К10-17-2б-Н90,"0,22 мкФ +80-20%",2,,,,ПЭ3 p23,
C24,К10-17-2б-Н90,"0,22 мкФ +80-20%",2,,,,ПЭ3 p23,
C25,К10-17-2б-Н90,"0,22 мкФ +80-20%",2,,,,ПЭ3 p23,
C26,К10-17-2б-Н90,"0,22 мкФ +80-20%",2,,,,ПЭ3 p23,
C27,К10-17-2б-Н90,"0,22 мкФ +80-20%",2,,,,ПЭ3 p23,
C28,К10-17-2б-Н90,"0,22 мкФ +80-20%",2,,,,ПЭ3 p23,
C29,К10-17-2б-Н90,"0,22 мкФ +80-20%",2,,,,ПЭ3 p23,
C30,К10-17-2б-Н90,"0,22 мкФ +80-20%",2,,,,ПЭ3 p23,
C31,К10-17-2б-Н90,"0,22 мкФ +80-20%",2,,,,ПЭ3 p23,
C32,К10-17-2б-Н90,"0,22 мкФ +80-20%",2,,,,ПЭ3 p23,
C33,К10-17-2б-Н90,"0,22 мкФ +80-20%",2,,,,ПЭ3 p23,
C34,К10-17-2б-Н90,"0,22 мкФ +80-20%",2,,,,ПЭ3 p23,
C35,К10-17-1б-М47,68 пФ ±10%,2,,,,ПЭ3 p23,
C36,К10-17-2б-Н90,"0,22 мкФ +80-20%",2,,,,ПЭ3 p23,
C37,К10-17-2б-Н90,"0,22 мкФ +80-20%",2,,,,ПЭ3 p23,
C38,К10-17-2б-Н90,"0,22 мкФ +80-20%",2,,,,ПЭ3 p23,
C39,К10-17-2б-Н90,"0,22 мкФ +80-20%",2,,,,ПЭ3 p23,
C40,К10-17-1б-М47,27 пФ ±10%,2,,,,ПЭ3 p23,
C41,К10-17-2б-Н90,"0,22 мкФ +80-20%",2,,,,ПЭ3 p23,
C42,К10-17-2б-Н90,"0,22 мкФ +80-20%",2,,,,ПЭ3 p23,
C43,К10-17-2б-Н90,"0,22 мкФ +80-20%",2,,,,ПЭ3 p23,
C44,К10-17-2б-Н90,"0,22 мкФ +80-20%",2,,,,ПЭ3 p23,
C45,К10-17-1б-М1500,2200 пФ ±10%,2,,,,ПЭ3 p23,
C46,К10-17-1б-М1500,2200 пФ ±10%,2,,,,ПЭ3 p23,
C47,К10-17-1б-М1500,2200 пФ ±10%,2,,,,ПЭ3 p23,
C48,К10-17-2б-Н90,"0,22 мкФ +80-20%",2,,,,ПЭ3 p23,
C49,К10-17-2б-Н90,"0,22 мкФ +80-20%",2,,,,ПЭ3 p23,
C50,К10-17-2б-Н90,"0,22 мкФ +80-20%",2,,,,ПЭ3 p23,
C51,К10-17-2б-Н90,"0,22 мкФ +80-20%",2,,,,ПЭ3 p23,
C52,К10-17-2б-Н90,"0,22 мкФ +80-20%",2,,,,ПЭ3 p23,
C53,К10-17-2б-Н90,"0,22 мкФ +80-20%",2,,,,ПЭ3 p23,
C54,К10-17-1б-М1500,4700 пФ ±10%,2,,,,ПЭ3 p23,
C55,К10-17-2б-Н90,"0,22 мкФ +80-20%",2,,,,ПЭ3 p23,
C56,К10-17-2б-Н90,"0,22 мкФ +80-20%",2,,,,ПЭ3 p23,
C57,К10-17-2б-Н90,"0,22 мкФ +80-20%",2,,,,ПЭ3 p23,
C58,К10-17-2б-Н90,"0,22 мкФ +80-20%",2,,,,ПЭ3 p23,
C59,К10-17-2б-Н90,"0,22 мкФ +80-20%",2,,,,ПЭ3 p23,
C60,К10-17-2б-Н90,"0,22 мкФ +80-20%",2,,,,ПЭ3 p23,
C61,К10-17-2б-Н90,"0,22 мкФ +80-20%",2,,,,ПЭ3 p23,
C62,К10-17-2б-Н90,"0,22 мкФ +80-20%",2,,,,ПЭ3 p23,
C63,К10-17-2б-Н90,"0,22 мкФ +80-20%",2,,,,ПЭ3 p23,
C64,К10-17-1б-М47,120 пФ ±10%,2,,,,ПЭ3 p23,
C65,К10-17-2б-Н90,"0,22 мкФ +80-20%",2,,,,ПЭ3 p23,
C66,К10-17-2б-Н90,"0,22 мкФ +80-20%",2,,,,ПЭ3 p23,
C67,К10-17-2б-Н90,"0,22 мкФ +80-20%",2,,,,ПЭ3 p23,
C68,К10-17-2б-Н90,"0,22 мкФ +80-20%",2,,,,ПЭ3 p23,
C69,К10-17-2б-Н90,"0,22 мкФ +80-20%",2,,,,ПЭ3 p23,
C70,К10-17-1б-М47,100 пФ ±10%,2,,,,ПЭ3 p23,
C71,К10-17-2б-Н90,"0,22 мкФ +80-20%",2,,,,ПЭ3 p23,
C72,КМ-6Б-Н90,"2,2 мкФ +80-20%",2,,,,ПЭ3 p23,
C73,К10-17-2б-Н90,"0,22 мкФ +80-20%",2,,,,ПЭ3 p23,
C74,К10-17-1б-М1500,2200 пФ ±10%,2,,,,ПЭ3 p23,
C75,К10-17-2б-Н90,"0,22 мкФ +80-20%",2,,,,ПЭ3 p23,
C76,К10-17-2б-Н90,"0,22 мкФ +80-20%",2,,,,ПЭ3 p23,
C77,К10-17-2б-Н90,"0,22 мкФ +80-20%",2,,,,ПЭ3 p23,
C78,К10-17-1б-М47,51 пФ ±10%,2,,,,ПЭ3 p23,
C79,К10-17-1б-М47,51 пФ ±10%,2,,,,ПЭ3 p23,
C80,К10-17-2б-Н90,"0,22 мкФ +80-20%",2,,,,ПЭ3 p23,
C81,К10-17-2б-Н90,"0,22 мкФ +80-20%",2,,,,ПЭ3 p23,
C82,К10-17-1б-М47,51 пФ ±10%,2,,,,ПЭ3 p23,
C83,К10-17-1б-Н90,"0,1 мкФ +80-20%",2,,,,ПЭ3 p23,
C84,К10-17-1б-Н90,"0,1 мкФ +80-20%",2,,,,ПЭ3 p23,
C85,К10-17-2б-Н90,"0,22 мкФ +80-20%",2,,,,ПЭ3 p23,
C86,К10-17-1б-Н90,"0,1 мкФ +80-20%",2,,,,ПЭ3 p23,
C87,К10-17-2б-Н90,"0,22 мкФ +80-20%",2,,,,ПЭ3 p23,
D1,КР1818ВГ93,,40,20,21,40,ПЭ3 p23; Э3 sheet 1,
D2,КР565РУ5Г,,16,16,8,,ПЭ3 p23; Э3 sheet 1,
D3,КР565РУ5Г,,16,16,8,,ПЭ3 p23; Э3 sheet 1,
D4,К555ТЛ2,,14,7,14,,ПЭ3 p23; Э3 sheet 1,
D5,КР565РУ5Г,,16,16,8,,ПЭ3 p23; Э3 sheet 1,
D6,КР565РУ5Г,,16,16,8,,ПЭ3 p23; Э3 sheet 1,
D7,КР531ИД14,,16,8,16,,ПЭ3 p23; Э3 sheet 1,
D8,К155ЛП9,,14,7,14,,ПЭ3 p23; Э3 sheet 1,
D9,КР580ВИ53,,24,12,24,,ПЭ3 p23; Э3 sheet 1,
D10,К555ТМ9,,16,8,16,,ПЭ3 p23; Э3 sheet 1,
D11,КР565РУ5Г,,16,16,8,,ПЭ3 p23; Э3 sheet 1,
D12,КР565РУ5Г,,16,16,8,,ПЭ3 p23; Э3 sheet 1,
D13,КР556РТ12,,18,9,18,,ПЭ3 p23; Э3 sheet 1,ПЭ3 note: КДРВ
D14,К555ЛА3,,14,7,14,,ПЭ3 p23; Э3 sheet 1,
D15,К555ЛН1,,14,7,14,,ПЭ3 p23; Э3 sheet 1,
D16,К555ИЕ19,,14,7,14,,ПЭ3 p24; Э3 sheet 1,power table writes К565ИЕ19 - a slip
D17,К555ТМ2,,14,7,14,,ПЭ3 p24; Э3 sheet 1,
D18,КР565РУ5Г,,16,16,8,,ПЭ3 p23; Э3 sheet 1,
D19,КР565РУ5Г,,16,16,8,,ПЭ3 p23; Э3 sheet 1,
D20,КР1102АП15,,8,4,,8,ПЭ3 p24; Э3 sheet 1,no +5V; +12V on pin 8
D21,КР556РТ12,,18,9,18,,ПЭ3 p24; Э3 sheet 1,ПЭ3 note: СТРВ
D22,КР580ВВ51А,,28,4,26,,ПЭ3 p24; Э3 sheet 1,
D23,КР531ЛЕ1,,14,7,14,,ПЭ3 p24; Э3 sheet 1,power table: К555ЛЕ1
D24,КР531ТМ2,,14,7,14,,ПЭ3 p24; Э3 sheet 1,
D25,К555ЛР11,,14,7,14,,ПЭ3 p24; Э3 sheet 1,
D26,КР565РУ5Г,,16,16,8,,ПЭ3 p23; Э3 sheet 1,
D27,КР565РУ5Г,,16,16,8,,ПЭ3 p23; Э3 sheet 1,
D28,КР1102АП15,,8,4,,8,ПЭ3 p24; Э3 sheet 1,no +5V; +12V on pin 8
D29,К555ИЕ10,,16,8,16,,ПЭ3 p24; Э3 sheet 1,
D30,К555ИЕ10,,16,8,16,,ПЭ3 p24; Э3 sheet 1,
D31,К555ЛА4,,14,7,14,,ПЭ3 p24; Э3 sheet 1,
D32,К555КП15,,16,8,16,,ПЭ3 p24; Э3 sheet 1,
D33,К555ТМ2,,14,7,14,,ПЭ3 p24; Э3 sheet 1,
D34,КР565РУ5Г,,16,16,8,,ПЭ3 p23; Э3 sheet 1,
D35,КР565РУ5Г,,16,16,8,,ПЭ3 p23; Э3 sheet 1,
D36,К555ИЕ10,,16,8,16,,ПЭ3 p24; Э3 sheet 1,
D37,К555ИЕ10,,16,8,16,,ПЭ3 p24; Э3 sheet 1,
D38,КР580ВВ51А,,28,4,26,,ПЭ3 p24; Э3 sheet 1,
D39,К555ЛП5,,14,7,14,,ПЭ3 p24; Э3 sheet 1,
D40,К555ТМ8,,16,8,16,,ПЭ3 p24; Э3 sheet 1,
D41,К555ТМ2,,14,7,14,,ПЭ3 p24; Э3 sheet 1,
D42,К555ИЕ10,,16,8,16,,ПЭ3 p24; Э3 sheet 1,
D43,К555ТМ8,,16,8,16,,ПЭ3 p24; Э3 sheet 1,
D44,КР565РУ5Г,,16,16,8,,ПЭ3 p23; Э3 sheet 1,
D45,КР565РУ5Г,,16,16,8,,ПЭ3 p23; Э3 sheet 1,
D46,К555ИЕ19,,14,7,14,,ПЭ3 p24; Э3 sheet 1,power table writes К565ИЕ19 - a slip
D47,К555ТМ2,,14,7,14,,ПЭ3 p24; Э3 sheet 1,
D48,КР559ИП11,,16,8,16,,ПЭ3 p24; Э3 sheet 1,
D49,К555ИР16,,14,7,14,,ПЭ3 p24; Э3 sheet 1,
D50,К555ИР16,,14,7,14,,ПЭ3 p24; Э3 sheet 1,
D51,К555ИР23,,20,10,20,,ПЭ3 p24; Э3 sheet 1,
D52,К555АП5,,20,10,20,,ПЭ3 p24; Э3 sheet 1,
D53,КР565РУ5Г,,16,16,8,,ПЭ3 p23; Э3 sheet 1,
D54,КР565РУ5Г,,16,16,8,,ПЭ3 p23; Э3 sheet 1,
D55,К555ИР16,,14,7,14,,ПЭ3 p24; Э3 sheet 1,
D56,К555ИР16,,14,7,14,,ПЭ3 p24; Э3 sheet 1,
D57,К555ИР23,,20,10,20,,ПЭ3 p24; Э3 sheet 1,
D58,К555АП5,,20,10,20,,ПЭ3 p24; Э3 sheet 1,
D59,К555ИЕ19,,14,7,14,,ПЭ3 p24; Э3 sheet 1,power table writes К565ИЕ19 - a slip
D60,К555ТМ2,,14,7,14,,ПЭ3 p24; Э3 sheet 1,
D61,К555КП2,,16,8,16,,ПЭ3 p24; Э3 sheet 1,
D62,К555КП2,,16,8,16,,ПЭ3 p24; Э3 sheet 1,
D63,К555КП2,,16,8,16,,ПЭ3 p24; Э3 sheet 1,
D64,К555ЛН2,,14,7,14,,ПЭ3 p24; Э3 sheet 1,
D65,К573РФ4Б,,28,14,"1,28",,ПЭ3 p24; Э3 sheet 1,"type and contents by the variant table of sheet 1 (7004L/H or 7007L/H); power table reads +5V '1,2' - taken as 1,28, to check on the board"
D66,К555ЛА3,,14,7,14,,ПЭ3 p23; Э3 sheet 1,
D67,К555КП2,,16,8,16,,ПЭ3 p24; Э3 sheet 1,
D68,К555КП2,,16,8,16,,ПЭ3 p24; Э3 sheet 1,
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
